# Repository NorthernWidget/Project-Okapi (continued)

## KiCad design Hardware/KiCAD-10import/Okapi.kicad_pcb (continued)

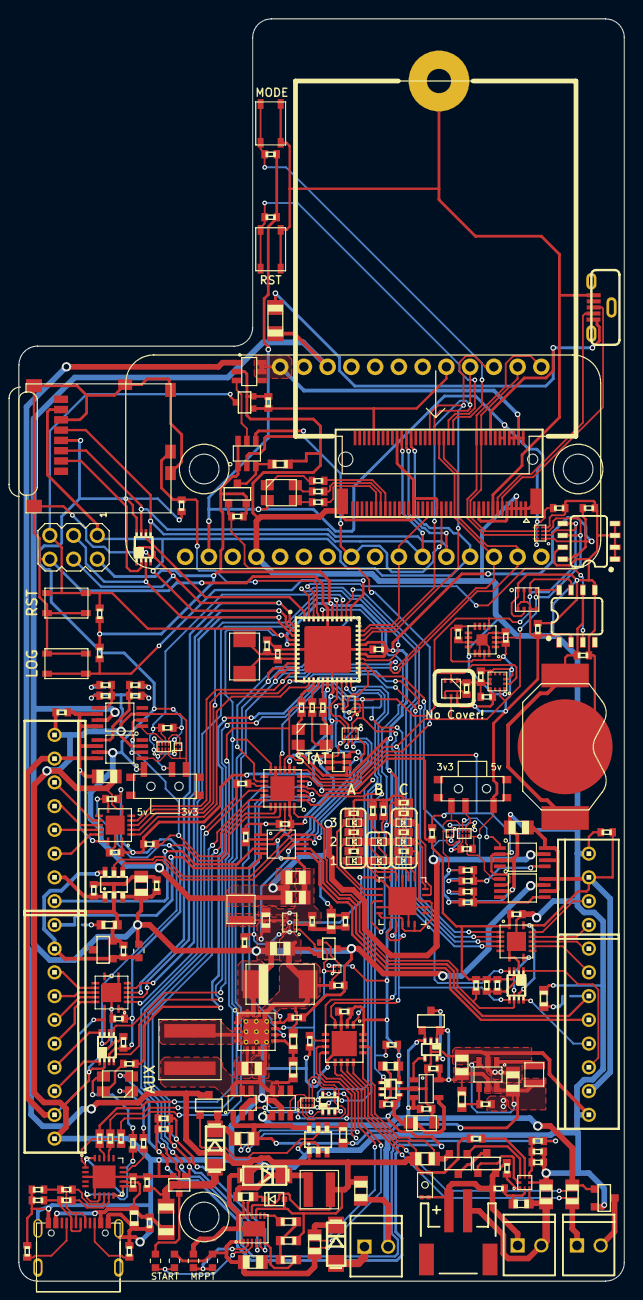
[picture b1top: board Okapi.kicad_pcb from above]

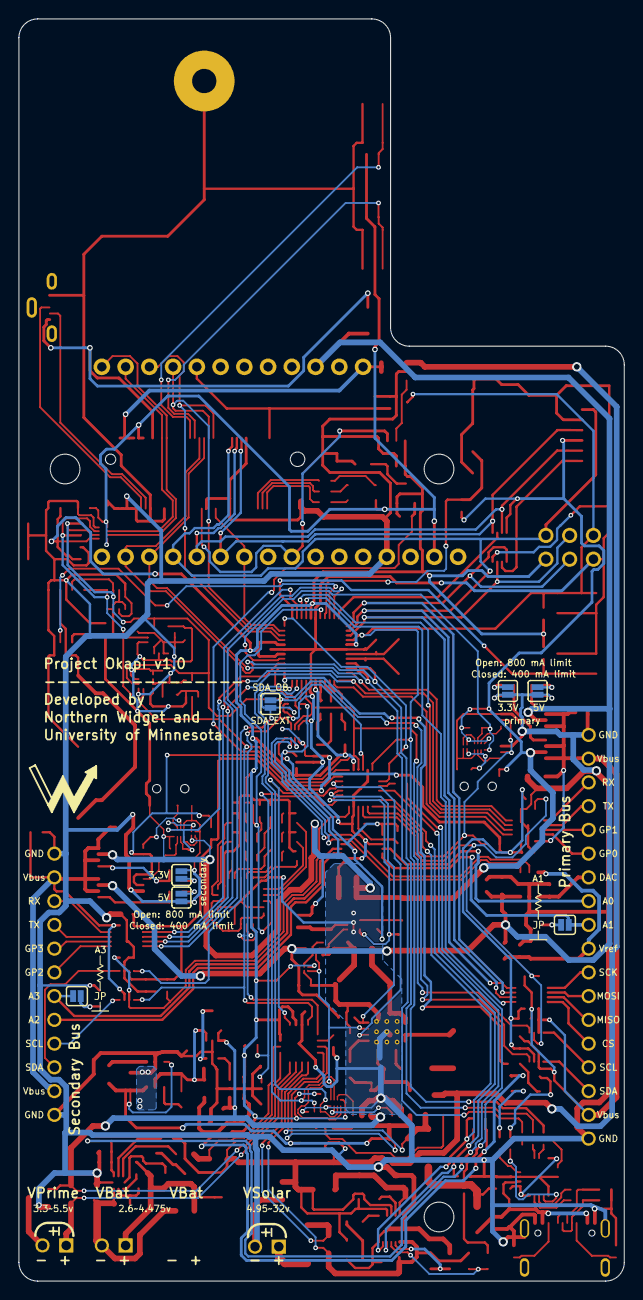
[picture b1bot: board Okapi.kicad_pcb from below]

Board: 2 copper layers, 64.8 x 135.0 mm, 250 parts (8 on the bottom side), 204 nets.

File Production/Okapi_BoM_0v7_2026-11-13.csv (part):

"Refs","Value","Footprint","Qty","MF","MPN","DIGIKEY","ALT_MF","ALT_MPN","ALT_DIGIKEY","DNP"
"BT1","BATTERY_COIN12MM","nw-cold-silicon:LINX_BAT-HLD-012-SMT","1","MPD","BK-916-TR","BK-916-CT-ND","","","",""
"C1,C18,C22","4.7uF","nw-cold-silicon:C0603","3","Murata","GRM188Z71C475KE21D","490-GRM188Z71C475KE21DCT-ND","","","",""
"C2,C3,C4,C7,C8,C9,C10,C14,C19,C20,C30","22uF","nw-cold-silicon:C0805","11","Murata","GRM219R61C226ME15L","490-9952-1-ND","","","",""
"C5","220uF","nw-cold-silicon:C2917","1","AVX","TPSY227K010R0100","478-5408-1-ND","","","",""
"C6,C33","68pF","nw-cold-silicon:C0402","2","Wurth","885012005060","732-7474-1-ND","","","",""
"C11,C13","1uF","nw-cold-silicon:C0603","2","Taiyo Yuden","TMK107B7105KA-T","587-2984-1-ND","","","",""
"C12,C17,C21,C25,C26,C27,C28,C29,C31,C32,C34,C35,C36,C37,C38,C39,C44,C45,C46,C47,C48,C50,C57","0.1uF","nw-cold-silicon:C0402","23","Murata","GCM155R71C104KA55D","490-4759-1-ND","","","",""
"C15,C16,C42","1uF","nw-cold-silicon:C0402","3","Samsung","CL05A105KA5NQNC","1276-1445-1-ND","","","",""
"C23,C24,C40,C41","12pF","nw-cold-silicon:C0402","4","TDK","CGA2B2C0G1H120J050BA","445-5585-1-ND","","","",""
"C43","100uF","nw-cold-silicon:C1206_TANT","1","Murata","GRM31CR61A107MEA8L","490-GRM31CR61A107MEA8LCT-ND","","","",""
"D1,D3","DIODEDO-214AC","nw-cold-silicon:DO214AC","2","Central Semiconductor","CMSH3-40MA TR13","CMSH3-40MATR13CT-ND","","","",""
"D2","DIODESOD-323","nw-cold-silicon:SOD323-R","1","Central Semiconductor","CMDSH2-3 TR","CMDSH2-3CT-ND","","","",""
"D4,D5,D7","CLVBA-FKA","nw-cold-silicon:CLVBA-FKA","3","Cree","CLVBA-FKA-CAEDH8BBB7A363","CLVBA-FKA-CAEDH8BBB7A363CT-ND","","","",""
"D6","LM4040","nw-cold-silicon:SOT23-3","1","Microchip","LM4040DYM3-2.5-TR","576-1047-1-ND","","","",""
"D8","BAT54C","nw-cold-silicon:SOT23-3","1","ON Semiconductor","BAT54CLT1G","BAT54CLT1GOSCT-ND","","","",""
"D9","DIODEDO-214AC","nw-cold-silicon:DO214AC","1","Diodes Incorporated","B340A-13-F","B340A-FDICT-ND","","","",""
"D10,D13,D16","LEDGREEN0603","nw-cold-silicon:LED_0603","3","Wurth","150060GS75000","732-4971-1-ND","","","",""
"D11,D14,D17","LEDYELLOW0603","nw-cold-silicon:LED_0603","3","Wurth","150060YS75000","732-4981-1-ND","","","",""
"D12,D18","LEDRED0603","nw-cold-silicon:LED_0603","2","Wurth","150060RS75000","732-4978-1-ND","","","",""
"F1,F2","PPTC1.5A","nw-cold-silicon:1206","2","Bourns","MF-NSMF150-2","MF-NSMF150-2CT-ND","","","",""
"H1,H2,H3","MOUNTING_HOLE4_NP","nw-cold-silicon:4_40","3","N/A","DNP","DNP","","","",""
"IC1","ATMEGA1284M","nw-cold-silicon:MLF44-TH","1","Atmel","ATMEGA1284P-MUR","ATMEGA1284P-MURCT-ND","","","",""
"ISP1","AVRISP-6","nw-cold-silicon:AVRISP","1","Amphenol","67997-206HLF","609-3234-ND","","","",""
"J1,J4","CONN_82.54_SCREW","nw-cold-silicon:1X08_SCREW","2","On Shore","OSTVN08A150","ED10566-ND","","","",""
"J2","CONN_102.54_SCREW","nw-cold-silicon:1X10_SCREW","1","On Shore","OSTVN10A150","ED10567-ND","","","",""
"J3","CONN_42.54_SCREW","nw-cold-silicon:1X04_SCREW","1","On Shore","OSTVN04A150","ED10563-ND","","","",""
"J5,J6,J7","CONN_022.54_SCREW","nw-cold-silicon:1X02_2.54_SCREWTERM","3","OnShore","OSTVN02A150","ED10561-ND","","","",""
"J8","JST_2MM_MALE","nw-cold-silicon:JST-2-SMD","1","JST","S2B-PH-SM4-TB(LF)(SN)","455-1749-1-ND","","","",""
"J9","B_SERIES_M.2EKEY_NOPROG","nw-cold-silicon:PARTICLE_M.2EKEY_NOPROG","1","TE","2199230-4","A115904CT-ND","","","",""
"J10","USB_C","nw-cold-silicon:USB_C_CUSB31-CFM2AX-01-X","1","GCT","USB4105-GF-A","2073-USB4105-GF-ACT-ND","","","",""
"JP1,JP2,JP3,JP4,JP5,JP6,JP7","JUMPER-SMT_2_NO_SILK","nw-cold-silicon:SMT-JUMPER_2_NO_SILK","7","","","","","","",""
"L1","6.8uH","nw-cold-silicon:1008","1","Wurth","74438323068","732-4849-1-ND","","","",""
"L2","10uH","nw-cold-silicon:WE-XHMI(6.65X6.45)","1","Wurth","74439346100","732-10707-1-ND","","","",""
"L3","1uH","nw-cold-silicon:WE-LQS(3X3)","1","Wurth","74404032010","732-5491-1-ND","","","",""
"L4","4.7uH","nw-cold-silicon:WE-MAIA(4.1X4.1)","1","Wurth","78438356047","732-11316-1-ND","","","",""
"Q1,Q2,Q6","DMG3404","nw-cold-silicon:SOT23-3","3","Diodes Incorporated","DMG3404L-7","DMG3404L-7DICT-ND","","","",""
"Q3,Q5","FDN360P","nw-cold-silicon:SOT23-3","2","onsemi","FDN360P","FDN360PCT-ND","","","",""
"Q4,Q7,Q8","2N7002","nw-cold-silicon:SOT323","3","ON Semiconductor","2N7002WT1G","2N7002WT1GOSCT-ND","","","",""
"R1,R5,R7,R8,R65,R66","180k","nw-cold-silicon:R0402","6","Yageo","RC0402FR-07180KL","311-180KLRCT-ND","Panasonic","ERJ-2RKF1803X","P180KLCT-ND",""
"R2,R4","1.62M","nw-cold-silicon:R0603","2","Vishay","CRCW06031M62FKEA","541-1.62MHCT-ND","Yageo","RC0603FR-071M62L","13-RC0603FR-071M62LCT-ND",""
"R3,R17","330k","nw-cold-silicon:R0603","2","Panasonic","ERJ-3EKF3303V","P330KHCT-ND","Stackpole","RMCF0603FT330K","RMCF0603FT330KCT-ND",""
"R6","820k","nw-cold-silicon:R0603","1","Yageo","RC0603FR-07820KL","311-820KHRCT-ND","Panasonic","ERJ-3EKF8203V","P820KHCT-ND",""
"R9,R53,R60,R64,R76,R77,R78,R79,R80","220R","nw-cold-silicon:R0402","9","TE","CRGCQ0402F220R","A129619CT-ND","Yageo","RC0402FR-07220RL","311-220LRCT-ND",""
"R10","3m","nw-cold-silicon:R0805","1","Rohm","PMR10EZPFV3L00","RHM.003AJCT-ND","Vishay","WFC08053L000FE66","541-WFC08053L000FE66CT-ND",""
"R11,R34,R35","27","nw-cold-silicon:R0402","3","Yageo","RC0402FR-0727RL","YAG3086CT-ND","Panasonic","ERJ-2RKF27R0X","P27.0LCT-ND",""
"R12,R15","1k","nw-cold-silicon:R0402","2","Yageo","RC0402FR-071KL","311-1.00KLRCT-ND","Panasonic","ERJ-2RKF1001X","P1.00KLCT-ND",""
"R13","180k","nw-cold-silicon:R0603","1","Panasonic","ERJ-3EKF1803V","P180KHCT-ND","Stackpole","RMCF0603FT180K","RMCF0603FT180KCT-ND",""
"R14","100R","nw-cold-silicon:R0402","1","Yageo","RC0402FR-07100RL","311-100LRCT-ND","Stackpole","RMCF0402FT100R","RMCF0402FT100RCT-ND",""
"R16","91k","nw-cold-silicon:R0603","1","Panasonic","ERJ-3EKF9102V","P91.0KHCT-ND","Yageo","RC0603FR-0791KL","311-91.0KHRCT-ND",""
"R18,R19,R23,R57,R58,R61,R63","100k","nw-cold-silicon:R0402","7","Yageo","RC0402FR-07100KL","311-100KLRCT-ND","Panasonic","ERJ-2RKF1003X","P100KLCT-ND",""
"R20","130k","nw-cold-silicon:R0603","1","Panasonic","ERJ-3EKF1303V","P130KHCT-ND","Stackpole","RMCF0603FT130K","RMCF0603FT130KCT-ND",""
"R21","1M","nw-cold-silicon:R0603","1","Panasonic","ERJ-3EKF1004V","P1.00MHCT-ND","Yageo","RC0603FR-071ML","311-1.00MHRCT-ND",""
"R22","143k","nw-cold-silicon:R0402_0603","1","Yageo","RC0603FR-07143KL","311-143KHRCT-ND","","","",""
"R24,R25,R41,R45,R46,R47,R52,R54,R67,R86,R87","10k","nw-cold-silicon:R0402","11","Yageo","RC0402FR-0710KL","311-10.0KLRCT-ND","Panasonic","ERJ-2RKF1002X","P10.0KLCT-ND",""
"R26,R27,R28,R29","232","nw-cold-silicon:R0402","4","Yageo","RC0402FR-07232RL","YAG3063CT-ND","Stackpole","RMCF0402FT232R","RMCF0402FT232RCT-ND",""
"R30,R31,R32,R33","464","nw-cold-silicon:R0402","4","Yageo","RC0402FR-07464RL","311-464LRCT-ND","Panasonic","ERJ-2RKF4640X","P464LCT-ND",""
"R36,R37,R38,R39,R40,R42,R43,R44","330","nw-cold-silicon:R0402","8","Yageo","RC0402FR-07330RL","311-330LRCT-ND","Panasonic","ERJ-2RKF3300X","P330LCT-ND",""
"R48","1k","nw-cold-silicon:R0402_0603","1","Yageo","RC0402FR-071KL","311-1.00KLRCT-ND","Panasonic","ERJ-2RKF1001X","P1.00KLCT-ND",""
"R49,R50","10k","nw-cold-silicon:R0603","2","Bourns","CRT0603-BY-1002ELF","CRT0603-BY-1002ELFCT-ND","Susumu","RG1608P-103-B-T5","RG16P10.0KBCT-ND",""
"R51","0","nw-cold-silicon:R0402","1","Panasonic","ERJ-2GE0R00X","P0.0JCT-ND","Yageo","RC0402JR-070RP","YAG1279CT-ND",""
"R55,R56,R59,R68","1M","nw-cold-silicon:R0402","4","Yageo","RC0402FR-071ML","311-1.00MLRCT-ND","Panasonic","ERJ-2RKF1004X","P1.00MLCT-ND",""
"R69","100k","nw-cold-silicon:R0402_0603","1","Yageo","RC0402FR-07100KL","311-100KLRCT-ND","Panasonic","ERJ-2RKF1003X","P100KLCT-ND",""
"R70","200k","nw-cold-silicon:R0402_0603","1","Panasonic","ERJ-2RKF2003X","P200KLCT-ND","Yageo","RC0402FR-07200KL","311-200KLRCT-ND",""
"R71","1M","nw-cold-silicon:R0402_0603","1","Yageo","RC0402FR-071ML","311-1.00MLRCT-ND","Panasonic","ERJ-2RKF1004X","P1.00MLCT-ND",""
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
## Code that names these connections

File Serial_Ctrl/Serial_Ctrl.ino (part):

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boolean Debug = false; //FIX!!
char ReadArray[25] = {0};

const uint8_t C1 = 19; //Control pins for V_HP
const uint8_t C0 = 18;

const uint8_t EN_BUS_PRIME = 23;  //Power enable lines for buses
const uint8_t EN_BUS_SEC = 22;

const uint8_t GPIO[4] = {12, 25, 3, 26}; //GPIO pins 0~3, 0,1 on primary bus, 2,3 on secondary bus. 0 and 2 PWM capable

const uint8_t Global_Int = 28; //Global interrupt from IO Expander
const uint8_t Log_Int = 27; //Interrupt for logging event

////////////////////////////////////SD////////////////////////////////////////
const uint8_t SD_CS = 4; //Define chip select for SD card
char FileNameC[11]; //Used for file handling
boolean SD_Init = false;

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boolean TestSD()
{
  boolean SDError = false;
  pinMode(SD_CS, OUTPUT);
  SPI.setDataMode(SPI_MODE0);
  SPI.setClockDivider(SPI_CLOCK_DIV2); //Sts SPI clock to 4 MHz for an 8 MHz system clock

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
